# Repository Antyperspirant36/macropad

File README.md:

# MacroPad by Antyperspirant36
A compact 15-key mechanical macropad with RGB and a knob.

## The Build

*The complete MacroPad build*

## Features
- 15 mechanical switches
- Alps EC11 rotary encoder
- RGB with SK6812MINI LEDs
- XIAO RP2040
- KMK firmware

## Hardware Details

### Schematic

*The circuit design*

### PCB

*PCB layout*

### Case

*Case design*

## Bill of Materials (BOM)
| Component | Footprint | Quantity | Notes |
|----------|-----------|----------|--------|
| Cherry MX Switches | SW_Cherry_MX_1.00u_PCB | 15x | Any MX-style switch |
| 1N4148 Diodes | D_DO-35_SOD27_P7.62mm_Horizontal | 15x | Through-hole |
| Alps EC11 Encoder | RotaryEncoder_Alps_EC11E-Switch_Vertical_H20mm | 1x | With mounting holes |
| SK6812MINI LEDs | LED_SK6812MINI_PLCC4_3.5x3.5mm_P1.75mm | 3x | RGB |
| XIAO RP2040 | XIAO-RP2040-DIP | 1x | Main controller |
| DSA Keycaps | 1u | 15x | Any MX compatible |
| M3x16mm Screws | - | 4x | Case assembly |
| M3x5mx4mm Heat-set Inserts | - | 4x | Case mounting |

## License
MIT

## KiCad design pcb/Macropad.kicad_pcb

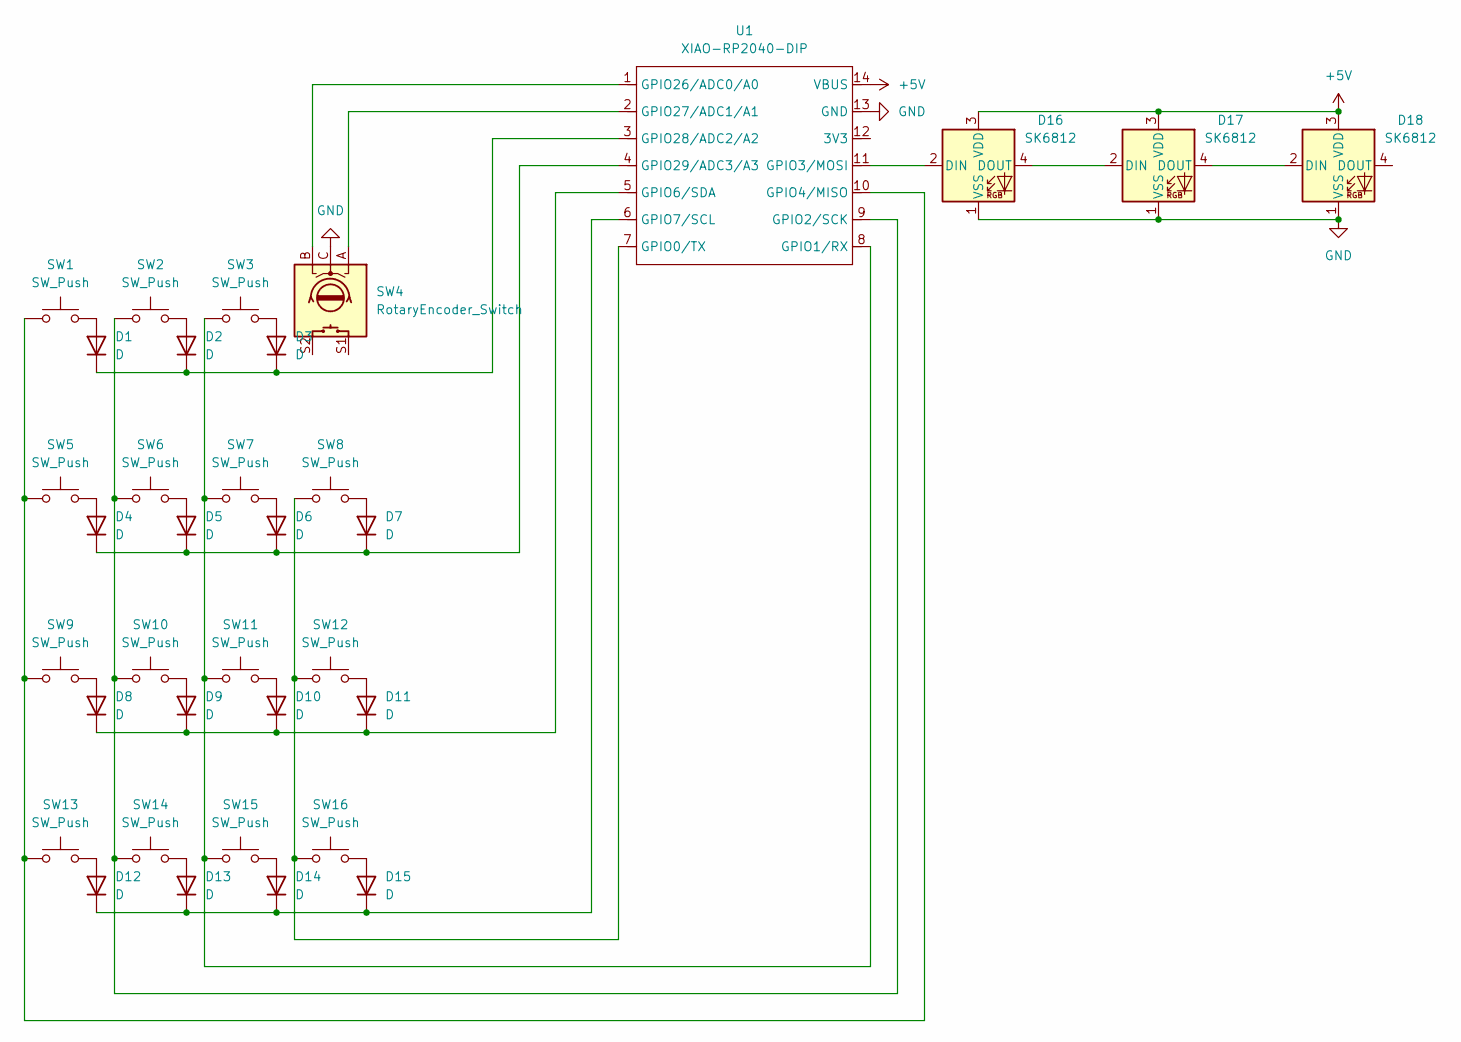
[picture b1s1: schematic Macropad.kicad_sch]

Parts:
D1, D2, D3, D4, D5, D6, D7, D8, D9, D10, D11, D12, D13, D14, D15: D; D_DO-35_SOD27_P7.62mm_Horizontal
D16, D17, D18: SK6812; LED_SK6812_PLCC4_5.0x5.0mm_P3.2mm
SW1, SW2, SW3, SW5, SW6, SW7, SW8, SW9, SW10, SW11, SW12, SW13, SW14, SW15, SW16: SW_Push; SW_Cherry_MX_1.00u_PCB
SW4: RotaryEncoder_Switch; RotaryEncoder_Alps_EC11E-Switch_Vertical_H20mm
U1: XIAO-RP2040-DIP

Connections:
+5V: D16.3 (VDD), D17.3 (VDD), D18.3 (VDD), U1.14 (VBUS)
GND: D16.1 (VSS), D17.1 (VSS), D18.1 (VSS), SW4.C, U1.13 (GND)
unnamed: D1.2 (A), SW1.2
unnamed: D1.1 (K), D2.1 (K), D3.1 (K), U1.3 (GPIO28/ADC2/A2)
unnamed: D2.2 (A), SW2.2
unnamed: D3.2 (A), SW3.2
unnamed: D4.2 (A), SW5.2
unnamed: D4.1 (K), D5.1 (K), D6.1 (K), D7.1 (K), U1.4 (GPIO29/ADC3/A3)
unnamed: D5.2 (A), SW6.2
unnamed: D6.2 (A), SW7.2
unnamed: D7.2 (A), SW8.2
unnamed: D8.2 (A), SW9.2
unnamed: D9.2 (A), SW10.2
unnamed: D10.2 (A), SW11.2
unnamed: D8.1 (K), D9.1 (K), D10.1 (K), D11.1 (K), U1.5 (GPIO6/SDA)
unnamed: D11.2 (A), SW12.2
unnamed: D12.2 (A), SW13.2
unnamed: D12.1 (K), D13.1 (K), D14.1 (K), D15.1 (K), U1.6 (GPIO7/SCL)
unnamed: D13.2 (A), SW14.2
unnamed: D14.2 (A), SW15.2
unnamed: D15.2 (A), SW16.2
unnamed: D16.2 (DIN), U1.11 (GPIO3/MOSI)
unnamed: D16.4 (DOUT), D17.2 (DIN)
unnamed: D17.4 (DOUT), D18.2 (DIN)
unnamed: SW8.1, SW12.1, SW16.1, U1.7 (GPIO0/TX)
unnamed: SW3.1, SW7.1, SW11.1, SW15.1, U1.8 (GPIO1/RX)
unnamed: SW2.1, SW6.1, SW10.1, SW14.1, U1.9 (GPIO2/SCK)
unnamed: SW1.1, SW5.1, SW9.1, SW13.1, U1.10 (GPIO4/MISO)
unnamed: SW4.B, U1.1 (GPIO26/ADC0/A0)
unnamed: SW4.A, U1.2 (GPIO27/ADC1/A1)

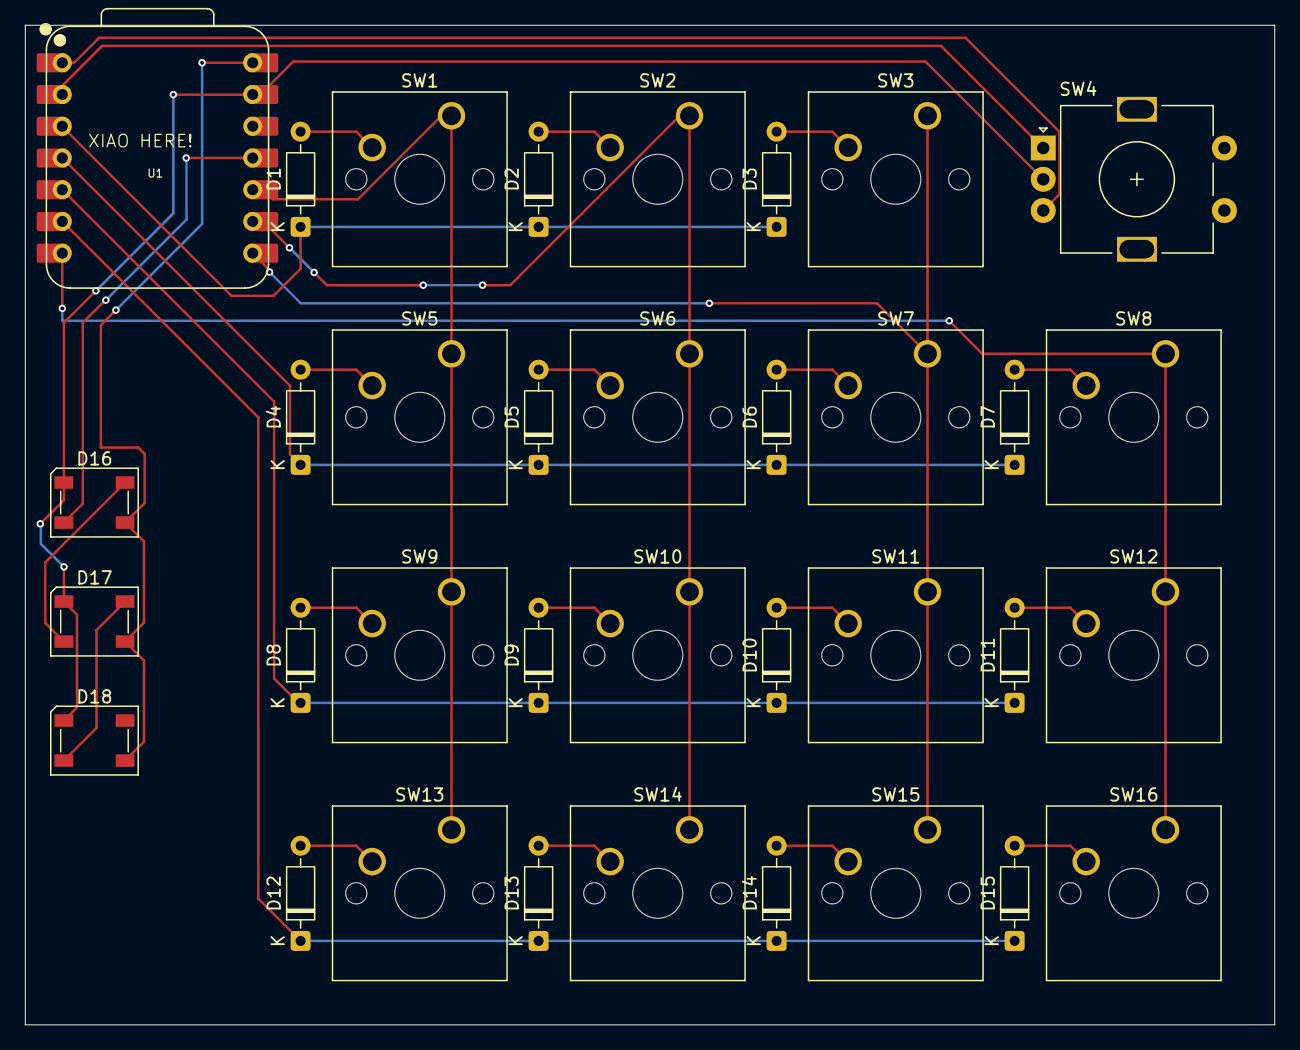
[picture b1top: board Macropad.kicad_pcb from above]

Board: 2 copper layers, 100.0 x 80.0 mm, 35 parts (0 on the bottom side), 30 nets.

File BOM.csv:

MX Switch, 15, MX-compatible mechanical switches, Any type
1N4148 Diodes, 15, D_DO-35 through-hole diodes, One per switch
EC11 Rotary Encoder, 1, Alps Switch_Vertical H20mm,	With mounting holes
SK6812MINI LEDs, 3, LED_SK6812MINI_PLCC4_3.5x3.5mm_P1.75mm, RGB
XIAO RP2040, 1, XIAO-RP2040-DIP, Main controller
Keycaps, 15, DSA profile keycaps , Any MX compatible
M3x Screws 16mm, 4, M3 Bolts, For Case assembly
Heatset Insert M3x5x4, 4, Brass inserts, For case assembly
3D Printed Case,1,Top and bottom shells,Designed in Fusion360

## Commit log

2025-12-10 Added Macropad Files
2025-12-10 Add README for MacroPad project
    Added detailed information about the MacroPad project, including features, hardware details, and a bill of materials.
2025-12-10 Add images
2025-12-12 Added BOM.csv
